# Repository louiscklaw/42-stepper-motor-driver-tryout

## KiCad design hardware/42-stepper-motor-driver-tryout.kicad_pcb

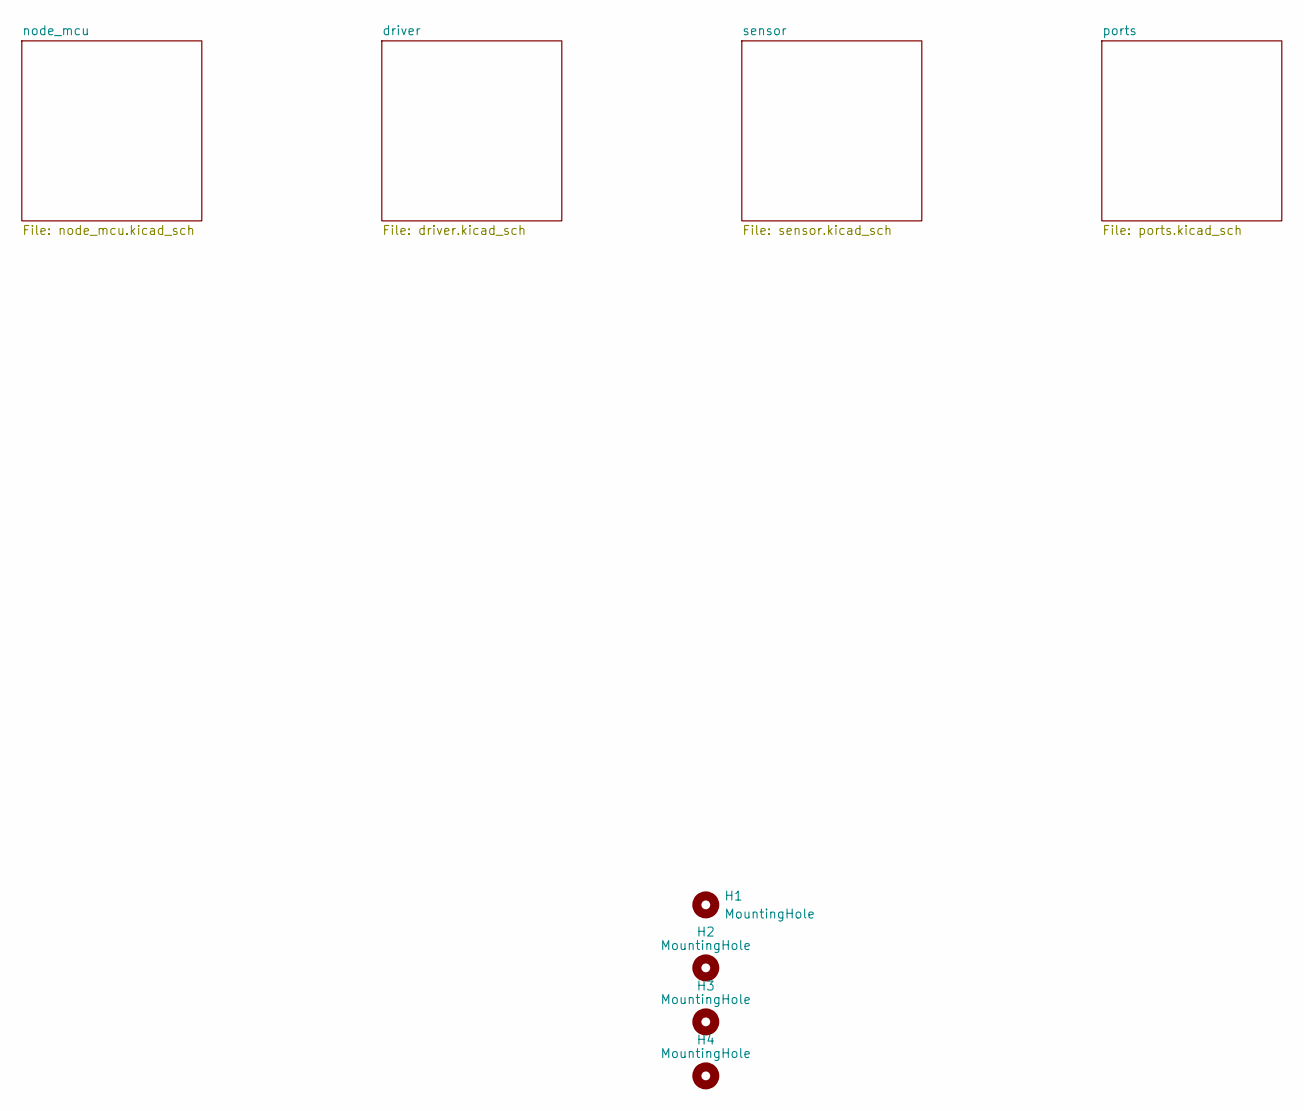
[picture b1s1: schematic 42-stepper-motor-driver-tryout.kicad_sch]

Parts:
H1, H2, H3, H4: MountingHole; MountingHole_2.7mm_M2.5,rpi_like

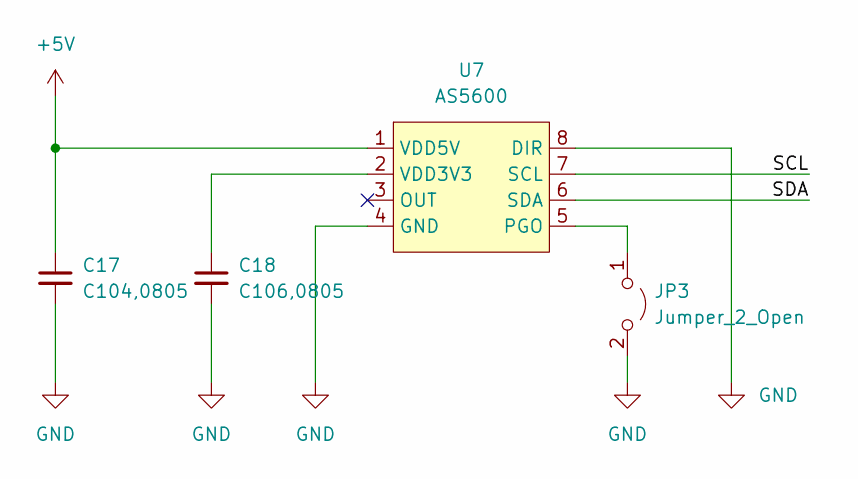
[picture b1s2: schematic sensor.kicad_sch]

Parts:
C17: C104,0805; C_0805_2012Metric
C18: C106,0805; C_0805_2012Metric
JP3: Jumper_2_Open; SolderJumper-2_P1.3mm_Open_RoundedPad1.0x1.5mm
U7: AS5600; SOIC-8-1EP_3.9x4.9mm_P1.27mm_EP2.29x3mm

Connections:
+5V: C17.1, U7.1 (VDD5V); also elsewhere on the board
/sensor/SCL: U7.7 (SCL)
/sensor/SDA: U7.6 (SDA)
GND: C17.2, C18.2, JP3.2 (B), U7.4 (GND), U7.8 (DIR); also elsewhere on the board
unnamed: C18.1, U7.2 (VDD3V3)
unnamed: JP3.1 (A), U7.5 (PGO)

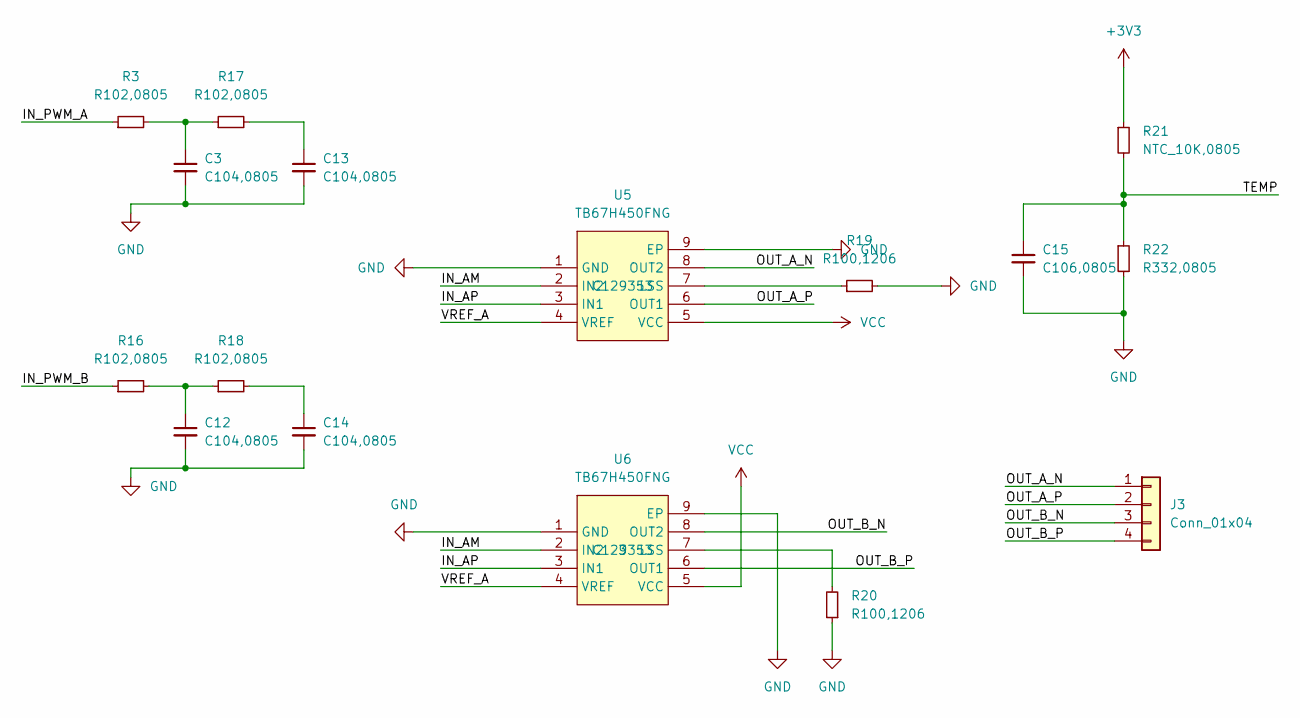
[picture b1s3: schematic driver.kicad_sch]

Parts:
C3, C12, C13, C14: C104,0805; C_0805_2012Metric
C15: C106,0805; C_0805_2012Metric
J3: Conn_01x04; PinHeader_1x04_P2.54mm_Vertical
R3, R16, R17, R18: R102,0805; R_0805_2012Metric
R19, R20: R100,1206; R_1206_3216Metric
R21: NTC_10K,0805; R_0805_2012Metric
R22: R332,0805; R_0805_2012Metric
U5, U6: TB67H450FNG; SOIC-8-1EP_3.9x4.9mm_P1.27mm_EP2.29x3mm; LCSC Part C129353

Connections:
+3V3: R21.1; also elsewhere on the board
/driver/IN_AM: U5.2 (IN2), U6.2 (IN2)
/driver/IN_AP: U5.3 (IN1), U6.3 (IN1)
/driver/IN_PWM_A: R3.1
/driver/IN_PWM_B: R16.1
/driver/OUT_A_N: J3.1, U5.8 (OUT2)
/driver/OUT_A_P: J3.2, U5.6 (OUT1)
/driver/OUT_B_N: J3.3, U6.8 (OUT2)
/driver/OUT_B_P: J3.4, U6.6 (OUT1)
/driver/TEMP: C15.1, R21.2, R22.1
/driver/VREF_A: U5.4 (VREF), U6.4 (VREF)
GND: C3.2, C12.2, C13.2, C14.2, C15.2, R19.2, R20.1, R22.2, U5.1 (GND), U5.9 (EP), U6.1 (GND), U6.9 (EP); also elsewhere on the board
unnamed: C3.1, R3.2, R17.1
unnamed: C12.1, R16.2, R18.1
unnamed: C13.1, R17.2
unnamed: C14.1, R18.2
unnamed: R19.1, U5.7 (LSS)
unnamed: R20.2, U6.7 (LSS)
VCC: U5.5 (VCC), U6.5 (VCC); also elsewhere on the board

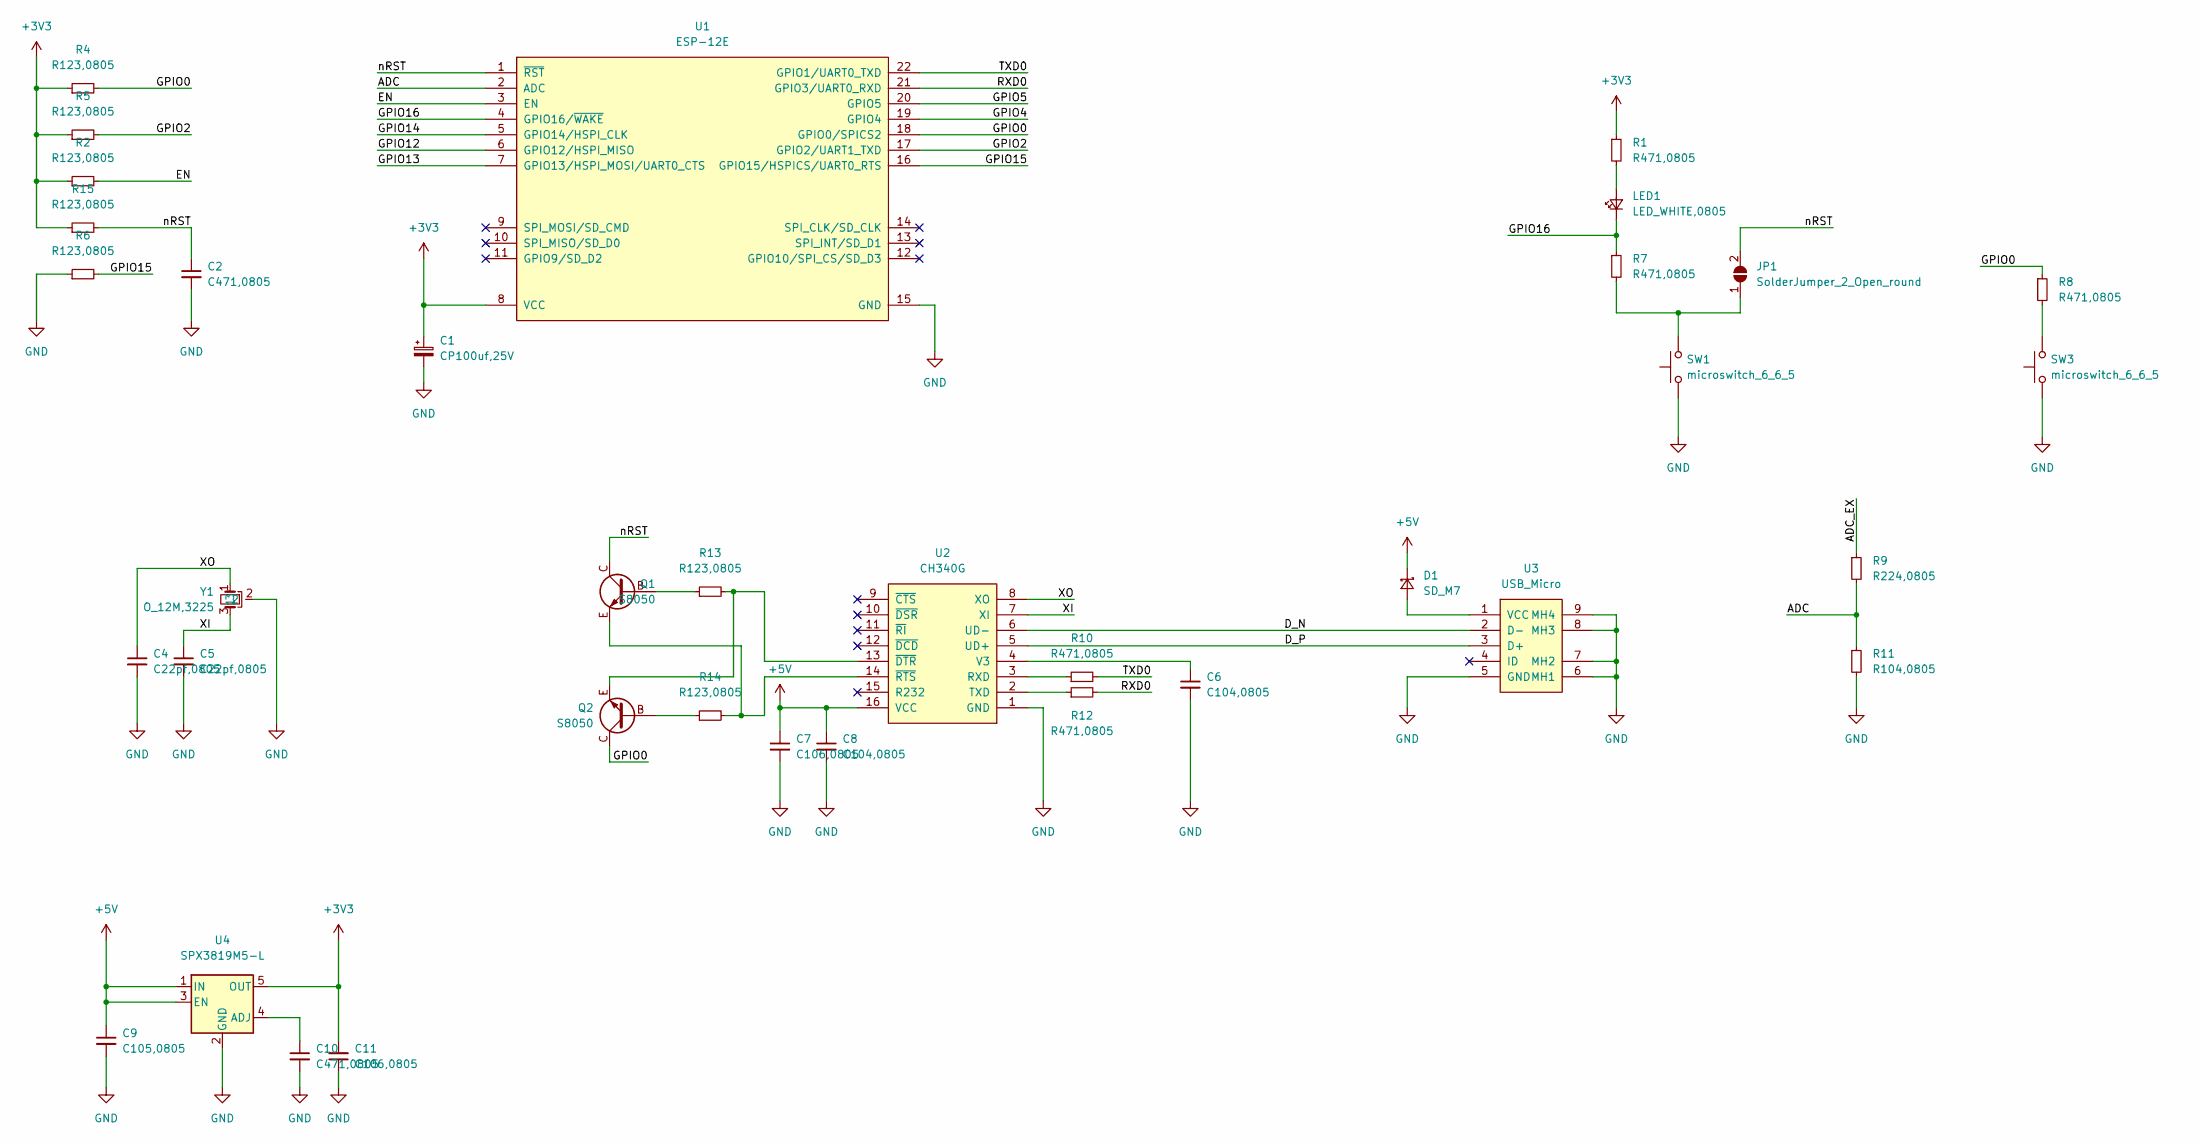
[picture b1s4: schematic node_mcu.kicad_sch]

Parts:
C1: CP100uf,25V; CP_EIA-3528-12_Kemet-T
C2, C10: C471,0805; C_0805_2012Metric
C4, C5: C22pf,0805; C_0805_2012Metric
C6, C8: C104,0805; C_0805_2012Metric
C7, C11: C106,0805; C_0805_2012Metric
C9: C105,0805; C_0805_2012Metric
D1: SD_M7; D_SMA
JP1: SolderJumper_2_Open_round; SolderJumper-2_P1.3mm_Open_RoundedPad1.0x1.5mm
LED1: LED_WHITE,0805; LED_0805_2012Metric
Q1, Q2: S8050; S8050,J3Y,SOT23
R1, R7, R8, R10, R12: R471,0805; R_0805_2012Metric
R2, R4, R5, R6, R13, R14, R15: R123,0805; R_0805_2012Metric
R9: R224,0805; R_0805_2012Metric
R11: R104,0805; R_0805_2012Metric
SW1, SW3: microswitch_6_6_5; SW_SPST_CK_RS282G05A3
U1: ESP-12E; ESP-12E_NO_HOLE
U2: CH340G; SOP-16_3.9x9.9mm_P1.27mm
U3: USB_Micro; USB_Micro-B_Molex-105017-0001
U4: SPX3819M5-L; SOT-23-5
Y1: O_12M,3225; OSC_3225

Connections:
+3V3: C1.1, C11.2, R1.1, R2.1, R4.1, R5.1, R15.1, U1.8 (VCC), U4.5 (OUT); also elsewhere on the board
+5V: C7.1, C8.1, C9.1, D1.1 (K), U2.16 (VCC), U4.1 (IN), U4.3 (EN); also elsewhere on the board
/node_mcu/ADC: R9.2, R11.1, U1.2 (ADC)
/node_mcu/ADC_EX: R9.1
/node_mcu/D_N: U2.6 (UD-), U3.2 (D-)
/node_mcu/D_P: U2.5 (UD+), U3.3 (D+)
/node_mcu/EN: R2.2, U1.3 (EN)
/node_mcu/GPIO0: Q2.C, R4.2, R8.1, U1.18 (GPIO0/SPICS2)
/node_mcu/GPIO2: R5.2, U1.17 (GPIO2/UART1_TXD)
/node_mcu/GPIO4: U1.19 (GPIO4)
/node_mcu/GPIO5: U1.20 (GPIO5)
/node_mcu/GPIO12: U1.6 (GPIO12/HSPI_MISO)
/node_mcu/GPIO13: U1.7 (GPIO13/HSPI_MOSI/UART0_CTS)
/node_mcu/GPIO14: U1.5 (GPIO14/HSPI_CLK)
/node_mcu/GPIO15: R6.2, U1.16 (GPIO15/HSPICS/UART0_RTS)
/node_mcu/GPIO16: LED1.1 (K), R7.1, U1.4 (GPIO16/~WAKE)
/node_mcu/RXD0: R12.2, U1.21 (GPIO3/UART0_RXD)
/node_mcu/TXD0: R10.2, U1.22 (GPIO1/UART0_TXD)
/node_mcu/XI: C5.1, U2.7 (XI), Y1.3
/node_mcu/XO: C4.1, U2.8 (XO), Y1.1
/node_mcu/nRST: C2.1, JP1.2 (B), Q1.C, R15.2, U1.1 (~RST)
GND: C1.2, C2.2, C4.2, C5.2, C6.2, C7.2, C8.2, C9.2, C10.2, C11.1, R6.1, R11.2, SW1.1, SW3.1, U1.15 (GND), U2.1 (GND), U3.5 (GND), U3.6 (MH1), U3.7 (MH2), U3.8 (MH3), U3.9 (MH4), U4.2 (GND), Y1.2; also elsewhere on the board
unnamed: C6.1, U2.4 (V3)
unnamed: C10.1, U4.4 (ADJ)
unnamed: D1.2 (A), U3.1 (VCC)
unnamed: JP1.1 (A), R7.2, SW1.2
unnamed: LED1.2 (A), R1.2
unnamed: Q1.B, R13.1
unnamed: Q1.E, R14.2, U2.14 (~RTS)
unnamed: Q2.B, R14.1
unnamed: Q2.E, R13.2, U2.13 (~DTR)
unnamed: R8.2, SW3.2
unnamed: R10.1, U2.3 (RXD)
unnamed: R12.1, U2.2 (TXD)

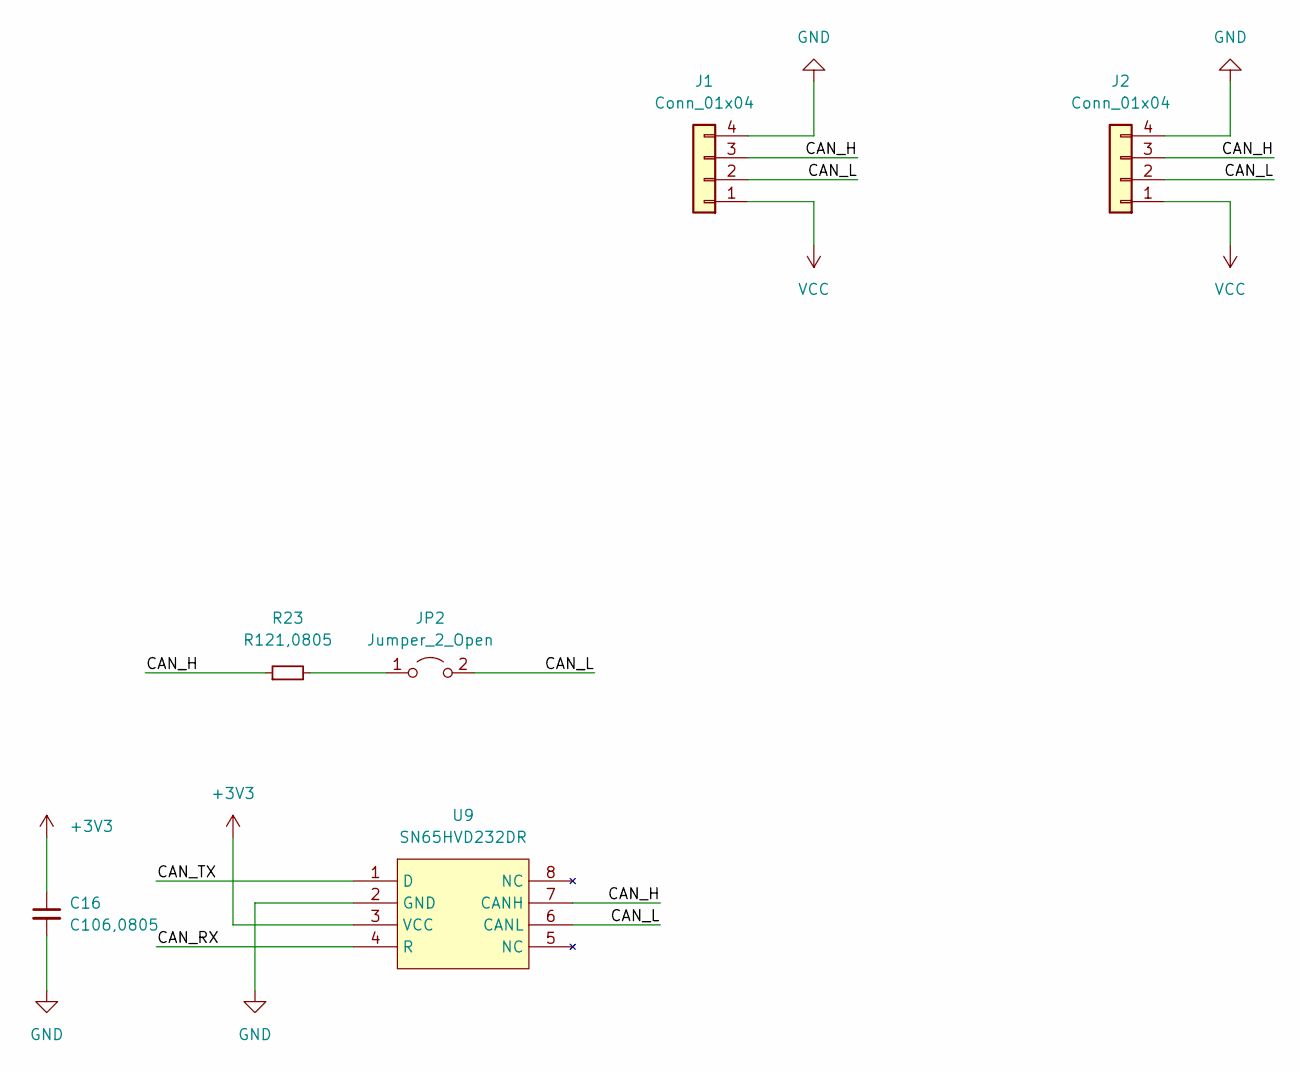
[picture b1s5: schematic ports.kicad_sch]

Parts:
C16: C106,0805; C_0805_2012Metric
J1, J2: Conn_01x04; PinHeader_1x04_P2.54mm_Vertical
JP2: Jumper_2_Open; SolderJumper-2_P1.3mm_Open_RoundedPad1.0x1.5mm
R23: R121,0805; R_0805_2012Metric
U9: SN65HVD232DR; SOIC-8-1EP_3.9x4.9mm_P1.27mm_EP2.29x3mm

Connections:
+3V3: C16.1, U9.3 (VCC); also elsewhere on the board
/ports/CAN_H: J1.3, J2.3, R23.1, U9.7 (CANH)
/ports/CAN_L: J1.2, J2.2, JP2.2 (B), U9.6 (CANL)
/ports/CAN_RX: U9.4 (R)
/ports/CAN_TX: U9.1 (D)
GND: C16.2, J1.4, J2.4, U9.2 (GND); also elsewhere on the board
unnamed: JP2.1 (A), R23.2
VCC: J1.1, J2.1; also elsewhere on the board

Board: 4 copper layers, 66 parts (13 on the bottom side), 48 nets, no tracks yet.

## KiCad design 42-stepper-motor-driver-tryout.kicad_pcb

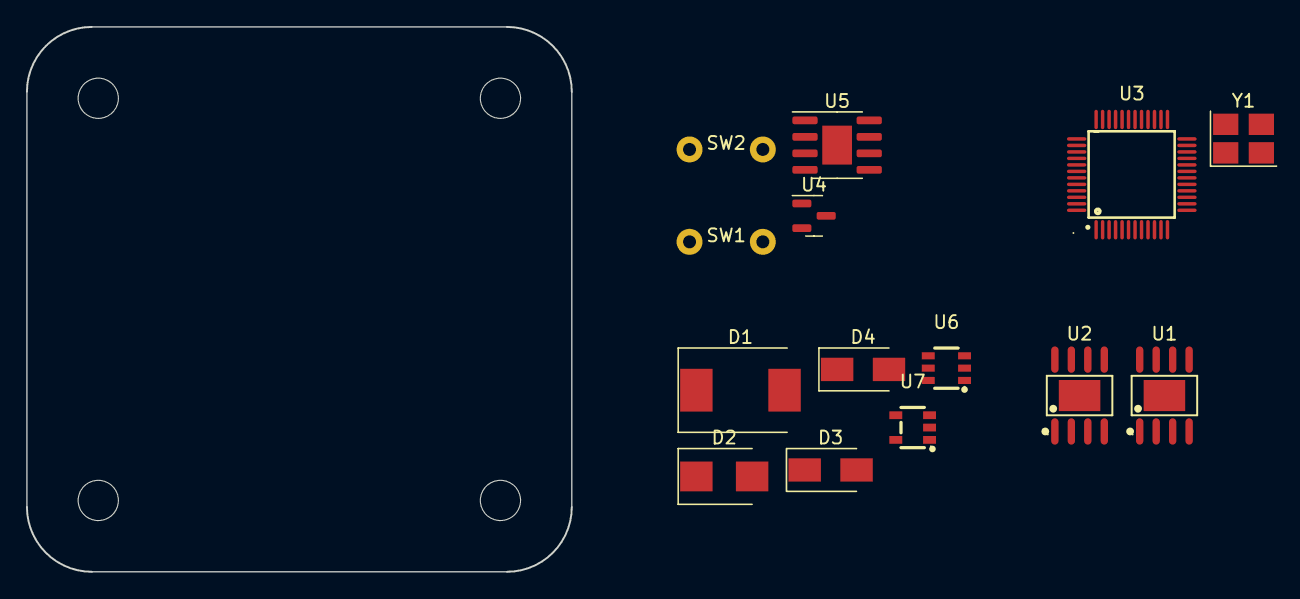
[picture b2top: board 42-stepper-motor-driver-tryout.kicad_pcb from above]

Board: 2 copper layers, 42.0 x 42.0 mm, 18 parts (0 on the bottom side), 12 nets, no tracks yet.

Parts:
D1: SS54; D_SMC
D2: SMBJ28CA; D_SMB
D3, D4: SD_1N5819_SS14; D_SMA
H1, H2, H3, H4: MountingHole; MountingHole_3.1mm_M3,rpi_like
SW1, SW2: microswitch_6_6_5
U1, U2: TB67H450FNG; TB67H450FNG,EL
U3: STM32F103CBT6; STM32F103CBT6TR
U4: TL431IDBZT; SOT-23
U5: SN65HVD232DR; SOIC-8-1EP_3.9x4.9mm_P1.27mm_EP2.29x3mm
U6: ME3116; ME3116AM6G
U7: LP2992; LP2992IM5-3.3_NOPB
Y1: O_12M,3225; OSC_3225

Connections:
+3V3: U3.1 (VBAT), U3.9 (VDDA), U3.24 (VDD_1), U3.36 (VDD_2), U3.48 (VDD_3), U5.3 (VCC), U7.5 (VOUT)
+5V: U7.1 (VIN), U7.3 (ON_OFF)
/drive/IN_AM: U1.2 (IN2), U2.2 (IN2)
/drive/IN_AP: U1.3 (IN1), U2.3 (IN1)
/drive/VREF_A: U1.4 (VREF), U2.4 (VREF)
GND: D2.1 (A1), D3.2 (A), SW1.1, SW2.1, U1.1 (GND), U1.9 (EP), U2.1 (GND), U2.9 (EP), U3.8 (VSSA), U3.35 (VSS_2), U3.47 (VSS_3), U4.3 (A), U5.2 (GND), U6.2 (GND), U7.2 (GND), Y1.2
unnamed: D3.1 (K), U6.6 (SW)
unnamed: D4.1 (K), U6.5 (IN)
unnamed: U4.1 (K), U4.2 (REF)
unnamed: U3.5 (PD0-OSC-IN), Y1.1
unnamed: U3.6 (PD1-OSC-OUT), Y1.3
VCC: D1.1 (K), D2.2 (A2), D4.2 (A), U1.5 (VCC), U2.5 (VCC)

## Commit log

2022-02-03 update,
2022-02-07 'update,'
